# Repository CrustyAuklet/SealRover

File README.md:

# SealRover
Project files for a remote control playback and recording vehicle for biological research

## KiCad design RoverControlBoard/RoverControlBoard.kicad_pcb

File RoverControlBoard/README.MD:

## Rover Control Board

This is the rover control board. It manages the rover systems and receives signals from the controller via a 2.4Ghz RC transmitter over SBUS.

Its main responsibilities are:
 * control camera panning
 * play audio files when requested
 * expandability with additional PWM outputs and switches
 
 Schematic:

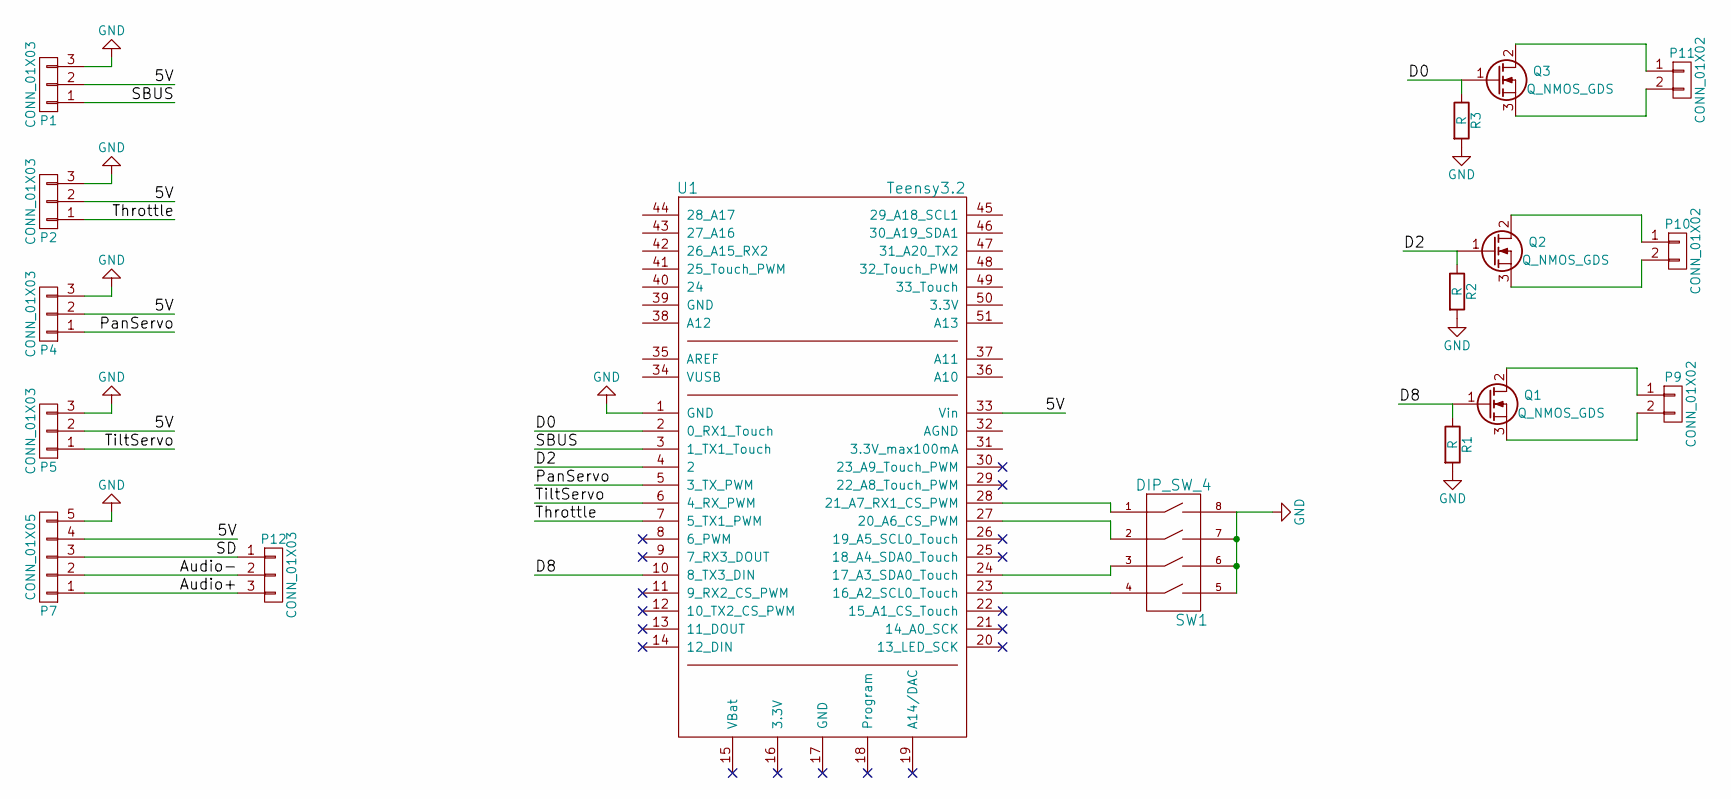
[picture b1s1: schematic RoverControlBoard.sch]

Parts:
P1, P2, P4, P5, P12: CONN_01X03; Pin_Header_Straight_1x03_Pitch2.54mm
P7: CONN_01X05; Pin_Header_Straight_1x05_Pitch2.54mm
P9, P10, P11: CONN_01X02; Pin_Header_Straight_1x02_Pitch2.54mm
Q1: Q_NMOS_GDS; Diode_TO-247_Dual_CommonCathode_Vertical
Q2, Q3: Q_NMOS_GDS; Diode_TO-220_Dual_CommonCathode_Vertical
R1, R2, R3: R; Resistor_Horizontal_RM7mm
SW1: DIP_SW_4; SW_DIP_x4_W7.62mm_Slide
U1: Teensy3.2; Teensy30_31_32_LC

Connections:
/5V: P1.2, P2.2, P4.2, P5.2, P7.4, U1.33 (Vin)
/Audio+: P7.1, P12.3
/Audio-: P7.2, P12.2
/D0: Q3.1 (G), R3.1, U1.2 (0_RX1_Touch)
/D2: Q2.1 (G), R2.1, U1.4 (2)
/D8: Q1.1 (G), R1.1, U1.10 (8_TX3_DIN)
/PanServo: P4.1, U1.5 (3_TX_PWM)
/SBUS: P1.1, U1.3 (1_TX1_Touch)
/SD: P7.3, P12.1
/Throttle: P2.1, U1.7 (5_TX1_PWM)
/TiltServo: P5.1, U1.6 (4_RX_PWM)
GND: P1.3, P2.3, P4.3, P5.3, P7.5, R1.2, R2.2, R3.2, SW1.5, SW1.6, SW1.7, SW1.8, U1.1 (GND)
unnamed: P9.1, Q1.2 (D)
unnamed: P9.2, Q1.3 (S)
unnamed: P10.1, Q2.2 (D)
unnamed: P10.2, Q2.3 (S)
unnamed: P11.1, Q3.2 (D)
unnamed: P11.2, Q3.3 (S)
unnamed: SW1.1, U1.28 (21_A7_RX1_CS_PWM)
unnamed: SW1.2, U1.27 (20_A6_CS_PWM)
unnamed: SW1.3, U1.24 (17_A3_SDA0_Touch)
unnamed: SW1.4, U1.23 (16_A2_SCL0_Touch)

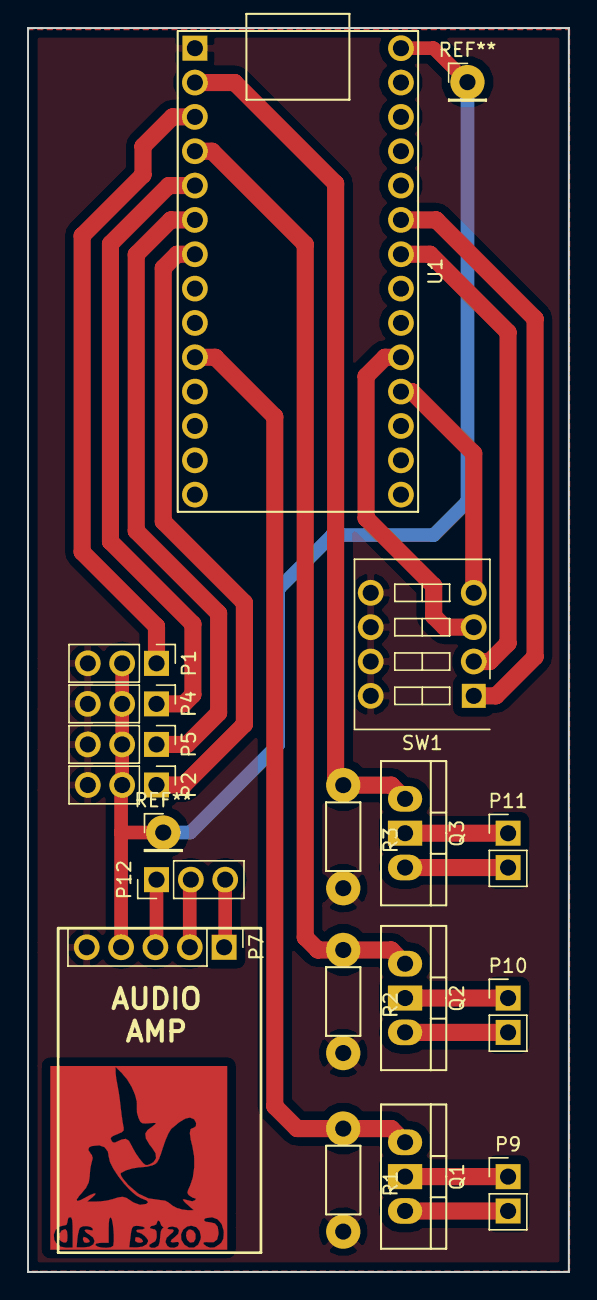
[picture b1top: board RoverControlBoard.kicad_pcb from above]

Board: 2 copper layers, 40.0 x 92.0 mm, 17 parts (0 on the bottom side), 22 nets.

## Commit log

2017-01-04 started kicad for rover control board
2017-01-04 adding media and rough drafts of arduino sketches
2017-01-07 finished baord layout
2017-01-08 changes track spacing on board for better etching in the future
2017-01-08 changed drill holes to reflect 3/64 drill available and adapted annular rings to leave more copper for soldering. Also increased pour isolation for better etching.
2017-01-09 modified firmware to reflect harware switch order
2017-01-09 Updated sound files
2017-01-10 Added schematic SVG
2017-01-10 Rename RoverControlBoard.sch.svg to RoverControlBoard_sch.svg
2017-01-10 new schematic picture, svgs are nogo
2017-05-22 initial commit of control board V2
2017-05-24 changed default channel values so that the sound will not play without button pressed
2017-05-24 changed code to handle regualr pan servo
2017-08-20 added project atomic part library. Finished audio circuit and power switching cirucit, as well as hooked up SD card.
2017-09-14 commiting altium control board v2
2017-10-02 finish schematic for V3 board
2017-10-02 fixed footprint for amp and started PCB file
2018-01-05 finished design of new pan tilt mechanism
2018-01-05 firmware update and PCB design changes (small)
2018-01-06 added pan and tilt feature with limits based on harware
2018-02-04 fixed bug where inputs stuck on lost signal
2018-02-04 added pt button channel and tried cleaned up light code
2018-02-04 added code to handle NMOS on pin 13 that is used to ensure radio does not turn on until the uC is initialized
2018-02-05 added throttle scaling to allow car creeping
2018-09-08 updates to rover firmware, to prevent runaway acceleration on signal loss and increase scaling factors
2018-09-08 started new version of the pan tild mount, with bearings
2018-09-08 created top plate for electronics enclosure
